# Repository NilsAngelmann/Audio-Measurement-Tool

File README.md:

# About

This fork focuses on the **stand-alone audio measurement tool** that was originally developed as part of the [“Making Music over the Internet”](https://github.com/StephanBorucki/MusizierenUeberDasInternet) project.

Here you will find detailed information such as the schematic, PCB layout, bill of materials, Arduino sketches, and usage instructions.

---

## Demo Video on YouTube 📺

---
## Files
- **Hardware:**
  - [2022](hardware/2022): Original version from 2022
    - Created with KiCad 8
    - Comments in German
    - Includes: Schematic, PCB Layout, Gerber Files, BOM
      
  - [2025](hardware/2025): Published version with corrections
    - Created with KiCad 9
    - Comments in English
    - Includes: Schematic
      
- **Firmware:**
  - [Measurement_03:](firmware/Measurement_03): Version 1.3
    - Measurement_03.ino: imports, pins, constants, variables, main loop of state machine
    - a_setup.ino: pin modes, welcome message on screen
    - b_menu.ino: menu to choose between error detection (DETECT) and latency measurement (BURST) mode
    - c_detect.ino: error detection (DETECT) mode
    - d_burst.ino: latency measurement (BURST) mode
   
> [!NOTE]
> Please refer to [Info2022](hardware/2022/Info2022.md) and [Info2025](hardware/2025/Info2025.md) before attempting to recreate this setup.

---
### License
This project is licensed under the [CERN Open Hardware License Version 2 – Permissive (CERN-OHL-P)](https://cern-ohl.web.cern.ch/).

Note: This license applies to the hardware design and firmware hosted here.
The printed article and its photos as published in Elektor remain subject to Elektor’s publishing rights.

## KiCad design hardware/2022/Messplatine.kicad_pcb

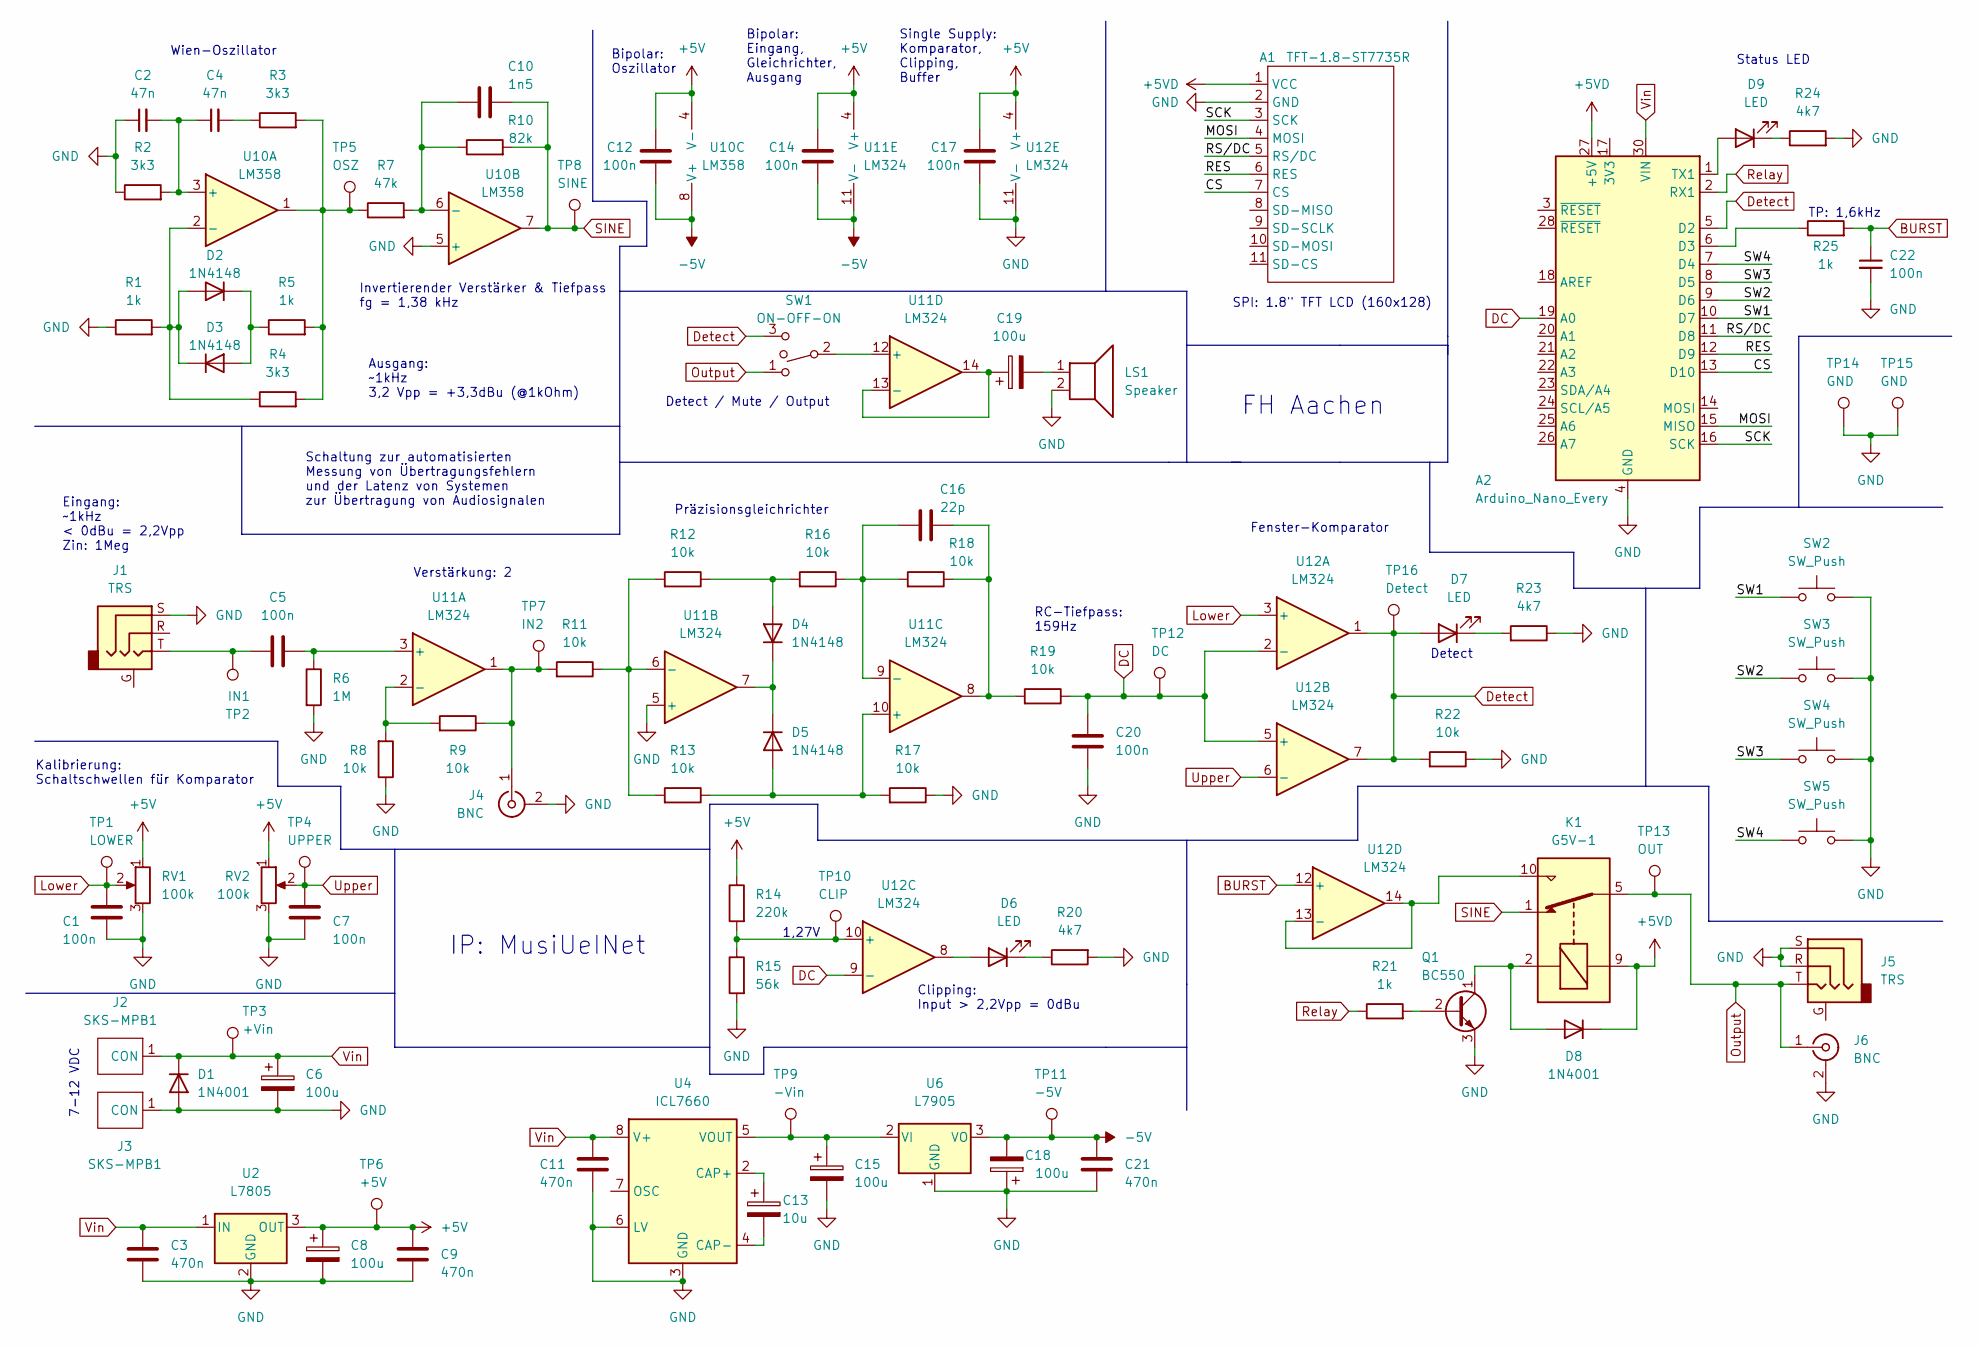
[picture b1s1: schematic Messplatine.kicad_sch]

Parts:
A1: TFT-1.8-ST7735R
A2: Arduino_Nano_Every; Arduino_Nano
C1, C5, C7, C12, C14, C17, C20, C22: 100n; C_Rect_L4.6mm_W3.0mm_P2.50mm_MKS02_FKP02
C2, C4: 47n; C_Rect_L4.6mm_W3.0mm_P2.50mm_MKS02_FKP02
C3, C9, C11, C21: 470n; C_Rect_L7.2mm_W3.5mm_P5.00mm_FKS2_FKP2_MKS2_MKP2
C6, C8, C15, C18, C19: 100u; C_Radial_D6.3mm_H11.0mm_P2.50mm
C10: 1n5; C_Rect_L7.2mm_W5.5mm_P5.00mm_FKS2_FKP2_MKS2_MKP2
C13: 10u; C_Radial_D5.0mm_H11.0mm_P2.00mm
C16: 22p; C_Rect_L7.0mm_W4.5mm_P5.00mm
D1, D8: 1N4001; D_DO-41_SOD81_P7.62mm_Horizontal
D2, D3, D4, D5: 1N4148; D_DO-35_SOD27_P7.62mm_Horizontal
D6, D7, D9: LED; LED_D3.0mm_Clear
J1, J5: TRS; Jack_6.35mm_Neutrik_NRJ6HF_Horizontal
J2, J3: SKS-MPB1
J4, J6: BNC; BKL-BNC
K1: G5V-1; Relay_SPDT_Omron_G5V-1
LS1: Speaker; TerminalBlock_Phoenix_MKDS-1,5-2-5.08_1x02_P5.08mm_Horizont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
Q1: BC550; TO-92
R1, R5, R21, R25: 1k; R_Axial_DIN0207_L6.3mm_D2.5mm_P10.16mm_Horizontal
R2, R3, R4: 3k3; R_Axial_DIN0207_L6.3mm_D2.5mm_P10.16mm_Horizontal
R6: 1M; R_Axial_DIN0207_L6.3mm_D2.5mm_P10.16mm_Horizontal
R7: 47k; R_Axial_DIN0207_L6.3mm_D2.5mm_P10.16mm_Horizontal
R8, R9, R11, R12, R13, R16, R17, R18, R19, R22: 10k; R_Axial_DIN0207_L6.3mm_D2.5mm_P10.16mm_Horizontal
R10: 82k; R_Axial_DIN0207_L6.3mm_D2.5mm_P10.16mm_Horizontal
R14: 220k; R_Axial_DIN0207_L6.3mm_D2.5mm_P10.16mm_Horizontal
R15: 56k; R_Axial_DIN0207_L6.3mm_D2.5mm_P10.16mm_Horizontal
R20, R23, R24: 4k7; R_Axial_DIN0207_L6.3mm_D2.5mm_P10.16mm_Horizontal
RV1, RV2: 100k; Potentiometer_Alps_RK09K_Single_Vertical
SW1: ON-OFF-ON; Miyama-MS-167
SW2, SW3, SW4, SW5: SW_Push; SW_PUSH_6mm_H8mm
TP1: LOWER; PinHeader_1x01_P2.54mm_Vertical
TP2: IN1; PinHeader_1x01_P2.54mm_Vertical
TP3: +Vin; PinHeader_1x01_P2.54mm_Vertical
TP4: UPPER; PinHeader_1x01_P2.54mm_Vertical
TP5: OSZ; PinHeader_1x01_P2.54mm_Vertical
TP6: +5V; PinHeader_1x01_P2.54mm_Vertical
TP7: IN2; PinHeader_1x01_P2.54mm_Vertical
TP8: SINE; PinHeader_1x01_P2.54mm_Vertical
TP9: -Vin; PinHeader_1x01_P2.54mm_Vertical
TP10: CLIP; PinHeader_1x01_P2.54mm_Vertical
TP11: -5V; PinHeader_1x01_P2.54mm_Vertical
TP12: DC; PinHeader_1x01_P2.54mm_Vertical
TP13: OUT; PinHeader_1x01_P2.54mm_Vertical
TP14, TP15: GND; PinHeader_1x01_P2.54mm_Vertical
TP16: Detect; PinHeader_1x01_P2.54mm_Vertical
U2: L7805; TO-220-3_Vertical
U4: ICL7660; DIP-8_W10.16mm
U6: L7905; TO-220-3_Vertical
U10: LM358; DIP-8_W10.16mm
U11, U12: LM324; DIP-14_W10.16mm

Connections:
+5V: C8.1, C9.1, C12.2, C14.2, C17.2, R14.1, RV1.1, RV2.1, TP6.1, U2.3 (OUT), U10.4 (V-), U11.4 (V+), U12.4 (V+)
+5VD: A1.1 (VCC), A2.27 (+5V), D8.1 (K), K1.9
-5V: C12.1, C14.1, C18.2, C21.1, TP11.1, U6.3 (VO), U10.8 (V+), U11.11 (V-)
/CS: A1.7 (CS), A2.13 (D10)
/MOSI: A1.4 (MOSI), A2.15 (MISO)
/RES: A1.6 (RES), A2.12 (D9)
/RS/DC: A1.5 (RS/DC), A2.11 (D8)
/SCK: A1.3 (SCK), A2.16 (SCK)
/SW1: A2.10 (D7), SW2.1
/SW2: A2.9 (D6), SW3.1
/SW3: A2.8 (D5), SW4.1
/SW4: A2.7 (D4), SW5.1
BURST: C22.1, R25.2, U12.12 (+)
DC: A2.19 (A0), C20.2, R19.1, TP12.1, U12.2 (-), U12.5 (+), U12.9 (-)
Detect: A2.5 (D2), D7.2 (A), R22.2, SW1.3, TP16.1, U12.1, U12.7
Lower: C1.2, RV1.2, TP1.1, U12.3 (+)
unnamed: A2.1 (TX1), D9.2 (A)
unnamed: A2.6 (D3), R25.1
unnamed: C2.2, C4.1, R2.2, U10.3 (+)
unnamed: C4.2, R3.1
unnamed: C5.1, J1.T, TP2.1
unnamed: C5.2, R6.1, U11.3 (+)
unnamed: C10.1, R7.2, R10.1, U10.6 (-)
unnamed: C13.1, U4.2 (CAP+)
unnamed: C13.2, U4.4 (CAP-)
unnamed: C15.1, TP9.1, U4.5 (VOUT), U6.2 (VI)
unnamed: C16.1, R16.1, R18.2, U11.9 (-)
unnamed: C16.2, R18.1, R19.2, U11.8
unnamed: C19.1, U11.13 (-), U11.14
unnamed: C19.2, LS1.1
unnamed: D2.1 (K), D3.2 (A), R5.1
unnamed: D2.2 (A), D3.1 (K), R1.2, R4.1, U10.2 (-)
unnamed: D4.1 (K), D5.1 (K), U11.7
unnamed: D4.2 (A), R12.1, R16.2
unnamed: D5.2 (A), R13.1, R17.2, U11.10 (+)
unnamed: D6.1 (K), R20.1
unnamed: D6.2 (A), U12.8
unnamed: D7.1 (K), R23.2
unnamed: D8.2 (A), K1.2, Q1.1 (C)
unnamed: D9.1 (K), R24.1
unnamed: J4.1 (In), R9.1, R11.2, TP7.1, U11.1
unnamed: K1.10, U12.13 (-), U12.14
unnamed: Q1.2 (B), R21.2
unnamed: R3.2, R4.2, R5.2, R7.1, TP5.1, U10.1
unnamed: R8.2, R9.2, U11.2 (-)
unnamed: R11.1, R12.2, R13.2, U11.6 (-)
unnamed: R14.2, R15.1, TP10.1, U12.10 (+)
unnamed: SW1.2, U11.12 (+)
Output: J5.T, J6.1 (In), K1.5, K1.6, SW1.1, TP13.1
Relay: A2.2 (RX1), R21.1
SINE: C10.2, K1.1, R10.2, TP8.1, U10.7
Upper: C7.2, RV2.2, TP4.1, U12.6 (-)
Vin: A2.30 (VIN), C3.1, C6.1, C11.1, D1.1 (K), J2.1 (CON), TP3.1, U2.1 (IN), U4.8 (V+)

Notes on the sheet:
Status LED
Verstärkung: 2
Bipolar: Oszillator
TP: 1,6kHz
Clipping: Input > 2,2Vpp = 0dBu
Schaltung zur automatisierten Messung von Übertragungsfehlern und der Latenz von Systemen zur Übertragung von Audiosignalen
Wien-Oszillator
Ausgang: ~1kHz 3,2 Vpp = +3,3dBu (@1kOhm)
Detect
Fenster-Komparator
FH Aachen
Detect / Mute / Output
Kalibrierung: Schaltschwellen für Komparator
RC-Tiefpass: 159Hz
Bipolar: Eingang, Gleichrichter, Ausgang
IP: MusiUeINet
Präzisionsgleichrichter
Single Supply: Komparator, Clipping, Buffer
Eingang: ~1kHz < 0dBu = 2,2Vpp Zin: 1Meg
1,27V
Invertierender Verstärker & Tiefpass fg = 1,38 kHz
SPI: 1.8" TFT LCD (160x128)
7-12 VDC

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
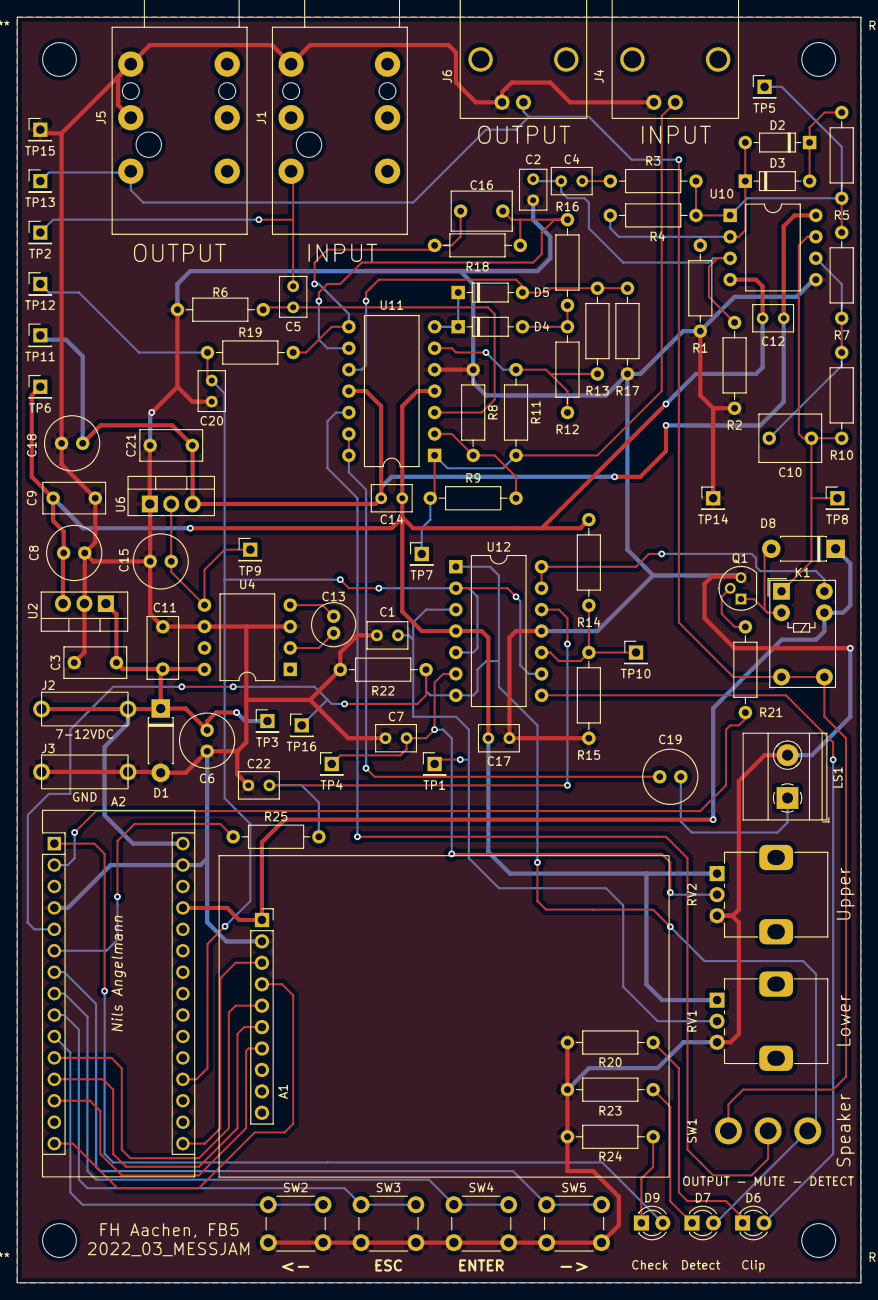
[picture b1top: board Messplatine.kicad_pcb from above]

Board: 2 copper layers, 100.0 x 150.0 mm, 96 parts (0 on the bottom side), 54 nets.

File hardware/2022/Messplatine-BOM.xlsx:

Ref | Value | Quantity | Link
A1 | TFT-1.8-ST7735R | 1 | https://www.reichelt.de/entwicklerboards-display-led-1-8-128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
A2 | Arduino_Nano_Every | 1 | https://www.reichelt.de/arduino-nano-every-atmega4809-mit-he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
A | Header | 2 | https://www.reichelt.de/50pol-stiftleiste-gerade-rm-2-54-sl-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
A | Sockets | 3 | https://www.reichelt.de/20pol-buchsenleiste-gerade-rm-2-54-b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
C1 C5 C7 C12 C14 C17 C20 C22 | 100n | 8 | https://www.reichelt.de/mks02-pet-kondensator-100-nf-10-63-v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
C10 | 1n5 | 1 | https://www.reichelt.de/mks2-pet-kondensator-1-5-f-5-63-vdc-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
C13 | 10u | 1 | https://www.reichelt.de/elko-radial-10-f-16-v-rm-2-5-85-c-20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
C16 | 22p | 1 | https://www.reichelt.de/vielschicht-kerko-22pf-200v-125-c-c3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
C2 C4 | 47n | 2 | https://www.reichelt.de/mks02-pet-kondensator-47-nf-10-63-vd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
C3 C9 C11 C21 | 470n | 4 | https://www.reichelt.de/folienkondensator-470nf-63v-rm5-mks2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
C6 C8 C15 C18 C19 | 100u | 5 | https://www.reichelt.de/elko-radial-100-f-16-v-rm-2-5-85-c-2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
D1 D8 | 1N4001 | 2 | https://www.reichelt.de/gleichrichterdiode-50-v-1-a-do-41-1n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
D2 D3 D4 D5 | 1N4148 | 4 | https://www.reichelt.de/schalt-diode-100-v-150-ma-do-35-1n-4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
D6 | LED, green | 1 | https://www.reichelt.de/led-3-mm-bedrahtet-gruen-6500-mcd-30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
D7 | LED, yellow | 1 | https://www.reichelt.de/led-3-mm-bedrahtet-gelb-850-mcd-30--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
D8 | LED, red | 1 | https://www.reichelt.de/led-3-mm-bedrahtet-rot-850-mcd-30--w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
J1 J5 | TRS | 2 | https://www.reichelt.de/klinkeneinbaubuchse-6-35-mm-stereo-n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
J2 | SKS-MPB1, black | 1 | https://www.reichelt.de/miniatur-pruefbuchse-2-mm-schwarz-mp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
J3 | SKS-MPB1, red | 1 | https://www.reichelt.de/miniatur-pruefbuchse-2-mm-rot-mpb-1-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
J4 J6 | BNC | 2 | https://www.reichelt.de/bnc-printeinbaubuchse-gewinkelt-50-o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
K1 | SPDT | 1 | https://www.reichelt.de/signalrelais-thd-5-vdc-1-a-1-wechsle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
LS1 | Screw terminal | 1 | https://www.reichelt.de/anschlussklemme-2-pol-rm-5-08-mm-90-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
LS | loudspeaker | 1 | https://www.reichelt.de/kleinlautsprecher-lsm-50m-k-f-0-5w-5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
Q1 | BC550 | 1 | https://www.reichelt.de/bipolartransistor-npn-45v-0-1a-hfe-4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
R1 R5 R21 R25 | 1k | 4 | https://www.reichelt.de/widerstand-metallschicht-1-00-kohm-0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
R10 | 82k | 1 | https://www.reichelt.de/widerstand-metallschicht-82-0-kohm-0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
R14 | 220k | 1 | https://www.reichelt.de/widerstand-metallschicht-220-kohm-02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
R15 | 56k | 1 | https://www.reichelt.de/widerstand-metallschicht-56-0-kohm-0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
R2 R3 R4 | 3k3 | 3 | https://www.reichelt.de/widerstand-metallschicht-3-30-kohm-0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
R20 R23 R24 | 4k7 | 3 | https://www.reichelt.de/widerstand-metallschicht-4-70-kohm-0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
R6 | 1M | 1 | https://www.reichelt.de/widerstand-metallschicht-1-0-mohm-02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
R7 | 47k | 1 | https://www.reichelt.de/widerstand-metallschicht-47-0-kohm-0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
R8 R9 R11 R12 R13 R16 R17 R18 R19 R22 | 10k | 10 | https://www.reichelt.de/widerstand-metallschicht-10-0-kohm-0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
RV1 RV2 | 100k | 2 | https://www.reichelt.de/drehpotentiometer-mono-100-kohm-line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
SW1 | ON-OFF-ON | 1 | https://www.reichelt.de/kippschalter-6-a-125-vac-1x-ein-aus-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
SW2 SW3 SW4 SW5 | SW_Push | 4 | https://www.reichelt.de/kurzhubtaster-6x6mm-hoehe-8-0mm-12v-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
U10 | LM358 | 1 | https://www.reichelt.de/operationsverstaerker-2-fach-0-4-v-s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
U0 | (Socket DIP8) | 1 | https://www.reichelt.de/praezisionsfassung-8-polig-rm-2-54-m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
U11 U12 | LM324 | 2 | https://www.reichelt.de/operationsverstaerker-quad-1-2-mhz-d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
U0 | (Socket DIP14) | 2 | https://www.reichelt.de/praezisionsfassung-14-polig-rm-2-54-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
U2 | L7805 | 1 | https://www.reichelt.de/spannungsregler-fest-5-v-to-220-mc-7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
U4 | ICL7660 | 1 | https://www.reichelt.de/dc-dc-einstellbar-1-5--12-v-1-5--12-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
U6 | L7905 | 1 | https://www.reichelt.de/ldo-festspannungsregler-5-vout-1-aou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
Z | PCB holder | 4 | https://www.reichelt.de/selbstklebender-abstandshalter-hoehe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

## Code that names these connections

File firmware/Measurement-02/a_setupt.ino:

void startup() {
  // Buttons
  pinMode(LEFT, INPUT_PULLUP);
  pinMode(ESC, INPUT_PULLUP);
  pinMode(ENTER, INPUT_PULLUP);
  pinMode(RIGHT, INPUT_PULLUP);

  // Burst Out
  pinMode(BURST, OUTPUT);

  //Detect
  pinMode(DETECT, INPUT);

  // Relay
  pinMode(RELAY, OUTPUT);
  digitalWrite(RELAY, HIGH);

  // LED
  pinMode(LED, OUTPUT);
  digitalWrite(LED, HIGH);

  // Display
  tft.initR(INITR_GREENTAB);
  tft.setRotation(3);
  tft.fillScreen(WHITE);
  tft.setTextColor(BLACK);
  tft.setFont(&FreeSansBold12pt7b);
  tft.setTextSize(1);
  tft.setCursor(20, 25);
  tft.print("FH Aachen");
  tft.setCursor(10, 55);
  tft.print("MusiUeINet");
  tft.setCursor(10, 85);
  tft.print("Messplatine");
  tft.setCursor(45, 115);
  tft.print("v 1.1");
  delay(3000);
  tft.fillScreen(BLACK);
  tft.setTextColor(WHITE, BLACK);
  digitalWrite(LED, LOW);
}

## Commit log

2025-10-05 Create LICENSE
    CC BY-NC 4.0
2025-10-05 Update LICENSE
2025-10-05 Rename IP_MusiUeINetEnglishSummaryByNilsAngelmann_v250126.pdf to MakingMusicOverTheInternet-Summary.pdf
2025-10-05 Rename PCB3.jpg to img/PCB3.jpg
2025-10-05 Rename Info.md to Info2025.md
2025-10-05 Rename Info.md to Info2022.md
2025-10-21 Updated license
2025-10-21 Revise firmware version and file references
    Updated firmware version and corrected file names in README.
2025-10-21 Change TIP note to NOTE in README
    Updated tip note to a more appropriate format.
2026-03-01 Add demo video section to README
    Added a section for a demo video on YouTube.
2026-03-01 Change YouTube video thumbnail in README
    Updated the demo video thumbnail in README.
